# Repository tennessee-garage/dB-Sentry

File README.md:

# dB-Sentry
Sound level monitoring, graphing and alerting for music events

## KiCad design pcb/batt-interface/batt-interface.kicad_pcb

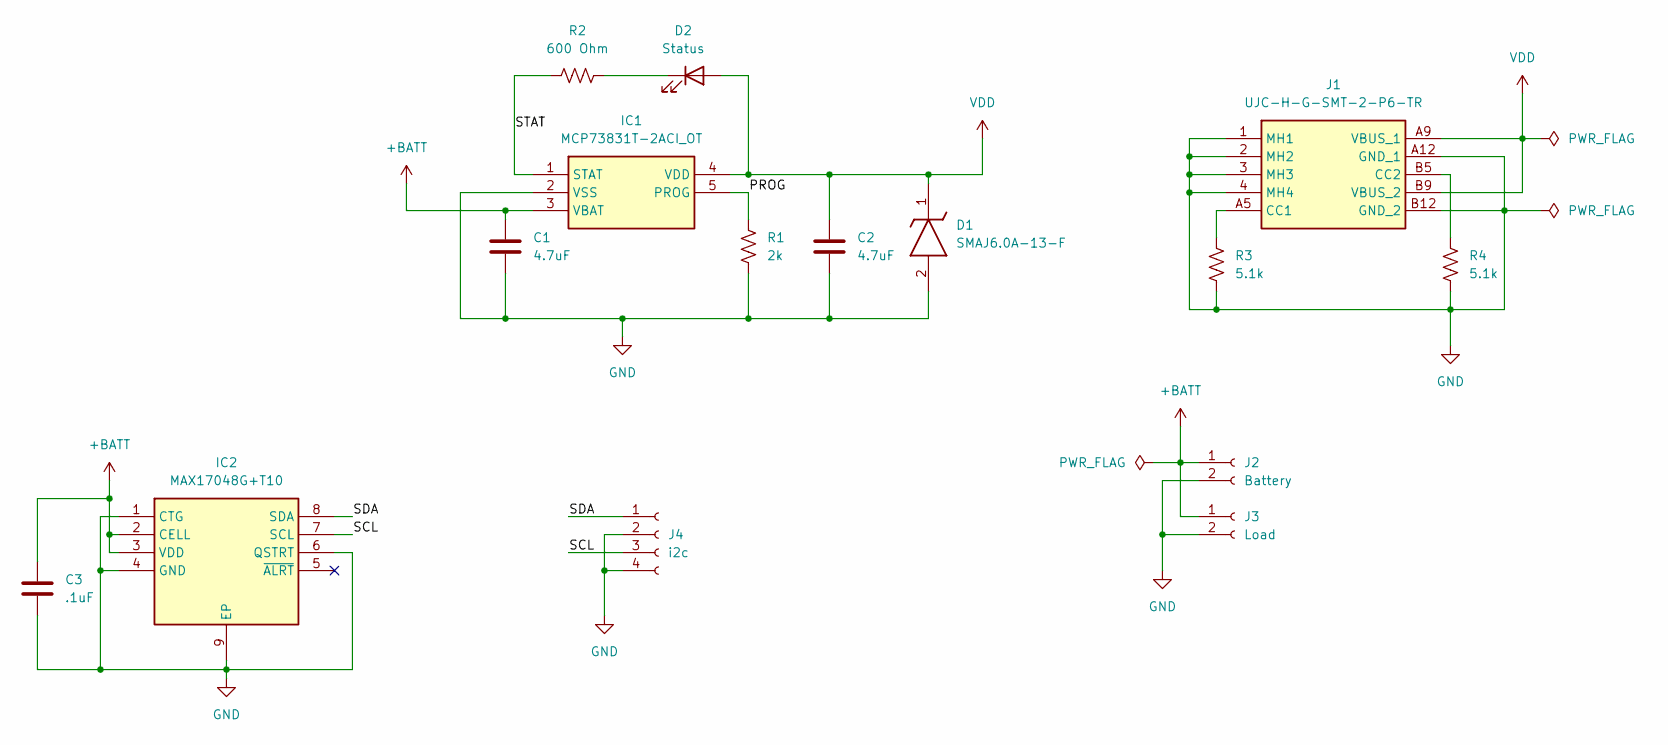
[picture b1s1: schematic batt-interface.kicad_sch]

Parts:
C1, C2: 4.7uF; C_0805_2012Metric_Pad1.18x1.45mm_HandSolder
C3: .1uF; C_0805_2012Metric_Pad1.18x1.45mm_HandSolder
D1: SMAJ6.0A-13-F; DIOM5226X240N; Mouser Part Number 621-SMAJ6.0A-13-F
D2: Status; LED_0805_2012Metric_Pad1.15x1.40mm_HandSolder
IC1: MCP73831T-2ACI_OT; SOT95P270X145-5N; Mouser Part Number 579-MCP73831T-2ACIOT
IC2: MAX17048G+T10; SON50P200X200X80-9N-D; Mouser Part Number 700-MAX17048G+T10
J1: UJC-H-G-SMT-2-P6-TR; UJCHGSMT2P6TR; Mouser Part Number 179-UJCHGSMT2P6TR
J2: Battery; JST_PH_S2B-PH-K_1x02_P2.00mm_Horizontal
J3: Load; JST_PH_S2B-PH-K_1x02_P2.00mm_Horizontal
J4: i2c; PinHeader_1x04_P2.54mm_Vertical
R1: 2k; R_0805_2012Metric_Pad1.20x1.40mm_HandSolder
R2: 600 Ohm; R_0805_2012Metric_Pad1.20x1.40mm_HandSolder
R3, R4: 5.1k; R_0805_2012Metric_Pad1.20x1.40mm_HandSolder

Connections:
+BATT: C1.1, C3.1, IC1.3 (VBAT), IC2.2 (CELL), IC2.3 (VDD), J2.1, J3.1
/PROG: IC1.5 (PROG), R1.1
/SCL: IC2.7 (SCL), J4.3
/SDA: IC2.8 (SDA), J4.1
/STAT: IC1.1 (STAT), R2.1
GND: C1.2, C2.2, C3.2, D1.2 (A), IC1.2 (VSS), IC2.1 (CTG), IC2.4 (GND), IC2.6 (QSTRT), IC2.9 (EP), J1.1 (MH1), J1.2 (MH2), J1.3 (MH3), J1.4 (MH4), J1.A12 (GND_1), J1.B12 (GND_2), J2.2, J3.2, J4.2, J4.4, R1.2, R3.2, R4.2
unnamed: D2.1 (K), R2.2
unnamed: J1.A5 (CC1), R3.1
unnamed: J1.B5 (CC2), R4.1
VDD: C2.1, D1.1 (K), D2.2 (A), IC1.4 (VDD), J1.A9 (VBUS_1), J1.B9 (VBUS_2)

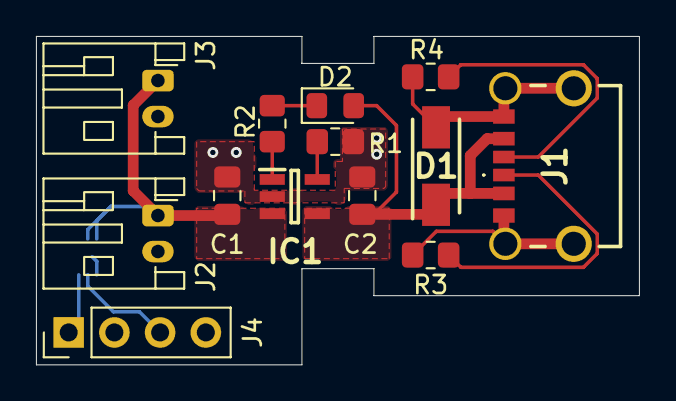
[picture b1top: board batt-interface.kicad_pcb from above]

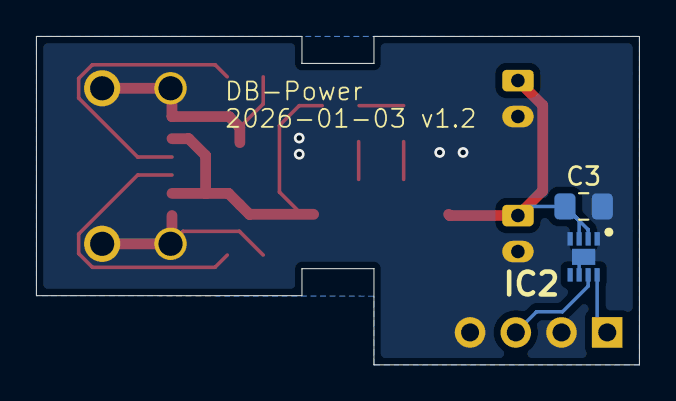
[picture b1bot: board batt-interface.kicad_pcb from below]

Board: 2 copper layers, 33.5 x 18.2 mm, 15 parts (2 on the bottom side), 10 nets.

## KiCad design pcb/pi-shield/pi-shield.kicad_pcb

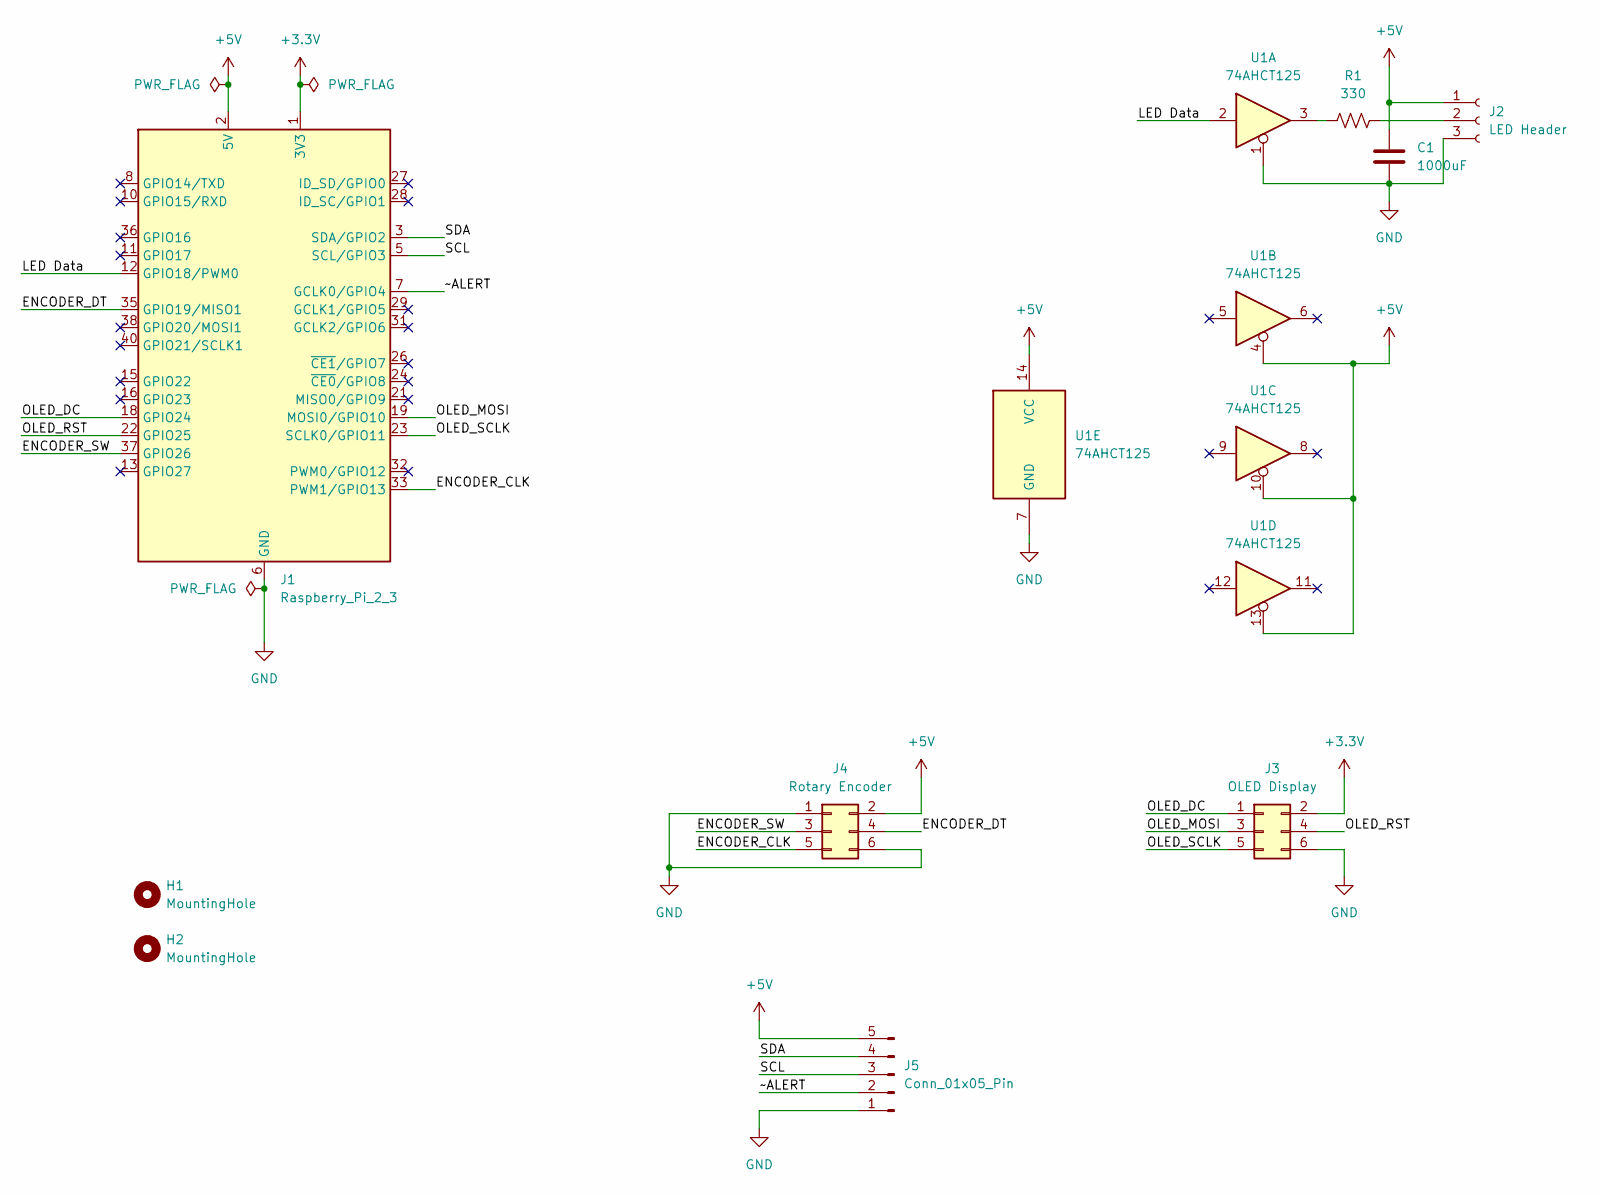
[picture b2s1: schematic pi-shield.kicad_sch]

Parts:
C1: 1000uF; C_Radial_D10.0mm_H16.0mm_P5.00mm
H1, H2: MountingHole; MountingHole_2.7mm_M2.5
J1: Raspberry_Pi_2_3; PinSocket_2x20_P2.54mm_Vertical
J2: LED Header; PinHeader_1x03_P2.54mm_Vertical
J3: OLED Display; PinHeader_2x03_P2.54mm_Vertical
J4: Rotary Encoder; PinHeader_2x03_P2.54mm_Vertical
J5: Conn_01x05_Pin; PinHeader_1x05_P2.54mm_Vertical
R1: 330; R_0805_2012Metric_Pad1.20x1.40mm_HandSolder
U1: 74AHCT125; TSSOP-14_4.4x5mm_P0.65mm

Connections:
+3.3V: J1.1 (3V3), J1.17 (3V3), J3.2
+5V: C1.1, J1.2 (5V), J1.4 (5V), J2.1, J4.2, J5.5, U1.4, U1.10, U1.13, U1.14 (VCC)
/ENCODER_CLK: J1.33 (PWM1/GPIO13), J4.5
/ENCODER_DT: J1.35 (GPIO19/MISO1), J4.4
/ENCODER_SW: J1.37 (GPIO26), J4.3
/LED Data: J1.12 (GPIO18/PWM0), U1.2
/OLED_DC: J1.18 (GPIO24), J3.1
/OLED_MOSI: J1.19 (MOSI0/GPIO10), J3.3
/OLED_RST: J1.22 (GPIO25), J3.4
/OLED_SCLK: J1.23 (SCLK0/GPIO11), J3.5
/SCL: J1.5 (SCL/GPIO3), J5.3
/SDA: J1.3 (SDA/GPIO2), J5.4
/~ALERT: J1.7 (GCLK0/GPIO4), J5.2
GND: C1.2, J1.6 (GND), J1.9 (GND), J1.14 (GND), J1.20 (GND), J1.25 (GND), J1.30 (GND), J1.34 (GND), J1.39 (GND), J2.3, J3.6, J4.1, J4.6, J5.1, U1.1, U1.7 (GND)
unnamed: J2.2, R1.2
unnamed: R1.1, U1.3

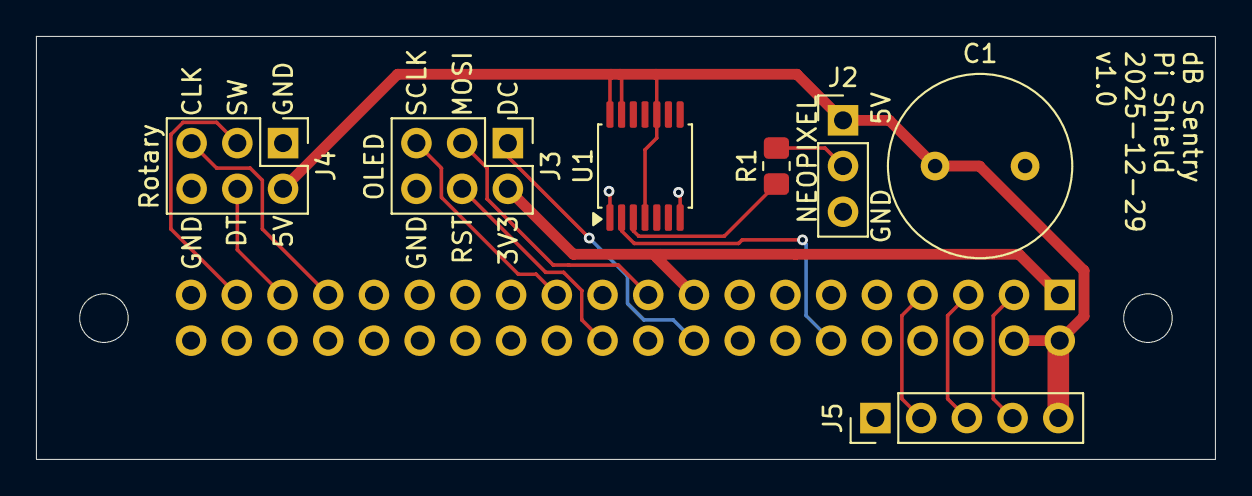
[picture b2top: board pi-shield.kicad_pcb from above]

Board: 2 copper layers, 65.5 x 23.5 mm, 10 parts (1 on the bottom side), 16 nets.

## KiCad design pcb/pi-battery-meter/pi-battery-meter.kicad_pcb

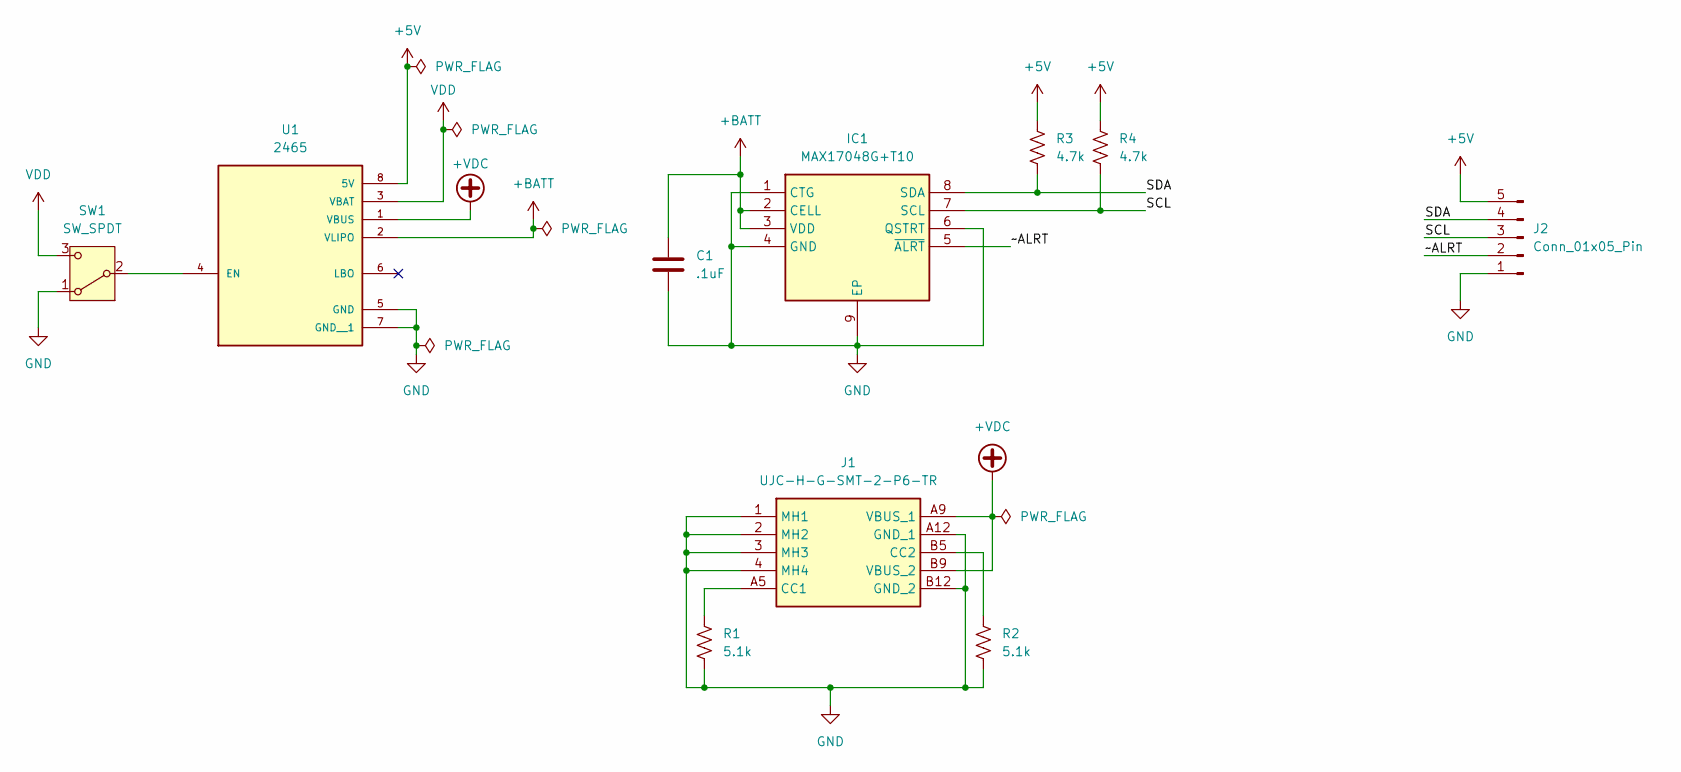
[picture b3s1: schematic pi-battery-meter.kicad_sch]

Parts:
C1: .1uF; C_0805_2012Metric_Pad1.18x1.45mm_HandSolder
IC1: MAX17048G+T10; SON50P200X200X80-9N-D; Mouser Part Number 700-MAX17048G+T10
J1: UJC-H-G-SMT-2-P6-TR; UJCHGSMT2P6TR; Mouser Part Number 179-UJCHGSMT2P6TR
J2: Conn_01x05_Pin; PinHeader_1x05_P2.54mm_Vertical
R1, R2: 5.1k; R_0805_2012Metric_Pad1.20x1.40mm_HandSolder
R3, R4: 4.7k; R_0805_2012Metric_Pad1.20x1.40mm_HandSolder
SW1: SW_SPDT; PinHeader_1x03_P2.54mm_Vertical
U1: 2465; MODULE_2465_NO_PTH; PARTREV B

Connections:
+5V: J2.5, R3.1, R4.1, U1.8 (5V)
+BATT: C1.1, IC1.2 (CELL), IC1.3 (VDD), U1.2 (VLIPO)
+VDC: J1.A9 (VBUS_1), J1.B9 (VBUS_2), U1.1 (VBUS)
/SCL: IC1.7 (SCL), J2.3, R4.2
/SDA: IC1.8 (SDA), J2.4, R3.2
/~ALRT: IC1.5 (~ALRT), J2.2
GND: C1.2, IC1.1 (CTG), IC1.4 (GND), IC1.6 (QSTRT), IC1.9 (EP), J1.1 (MH1), J1.2 (MH2), J1.3 (MH3), J1.4 (MH4), J1.A12 (GND_1), J1.B12 (GND_2), J2.1, R1.2, R2.2, SW1.1 (A), U1.5 (GND), U1.7 (GND__1)
unnamed: J1.A5 (CC1), R1.1
unnamed: J1.B5 (CC2), R2.1
unnamed: SW1.2 (B), U1.4 (EN)
VDD: SW1.3 (C), U1.3 (VBAT)

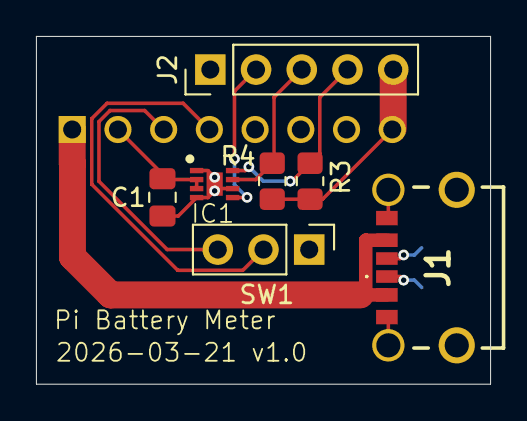
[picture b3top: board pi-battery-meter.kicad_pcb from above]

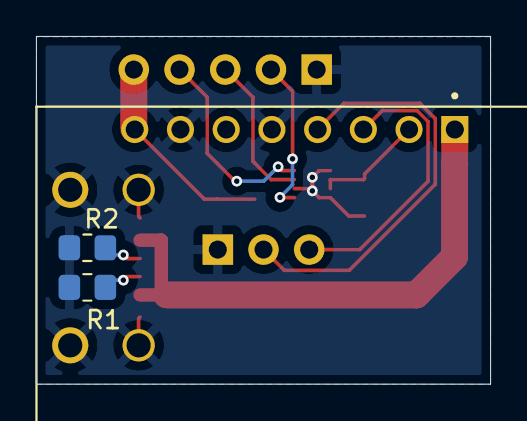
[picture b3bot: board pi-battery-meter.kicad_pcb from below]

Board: 2 copper layers, 25.2 x 19.3 mm, 10 parts (3 on the bottom side), 11 nets.

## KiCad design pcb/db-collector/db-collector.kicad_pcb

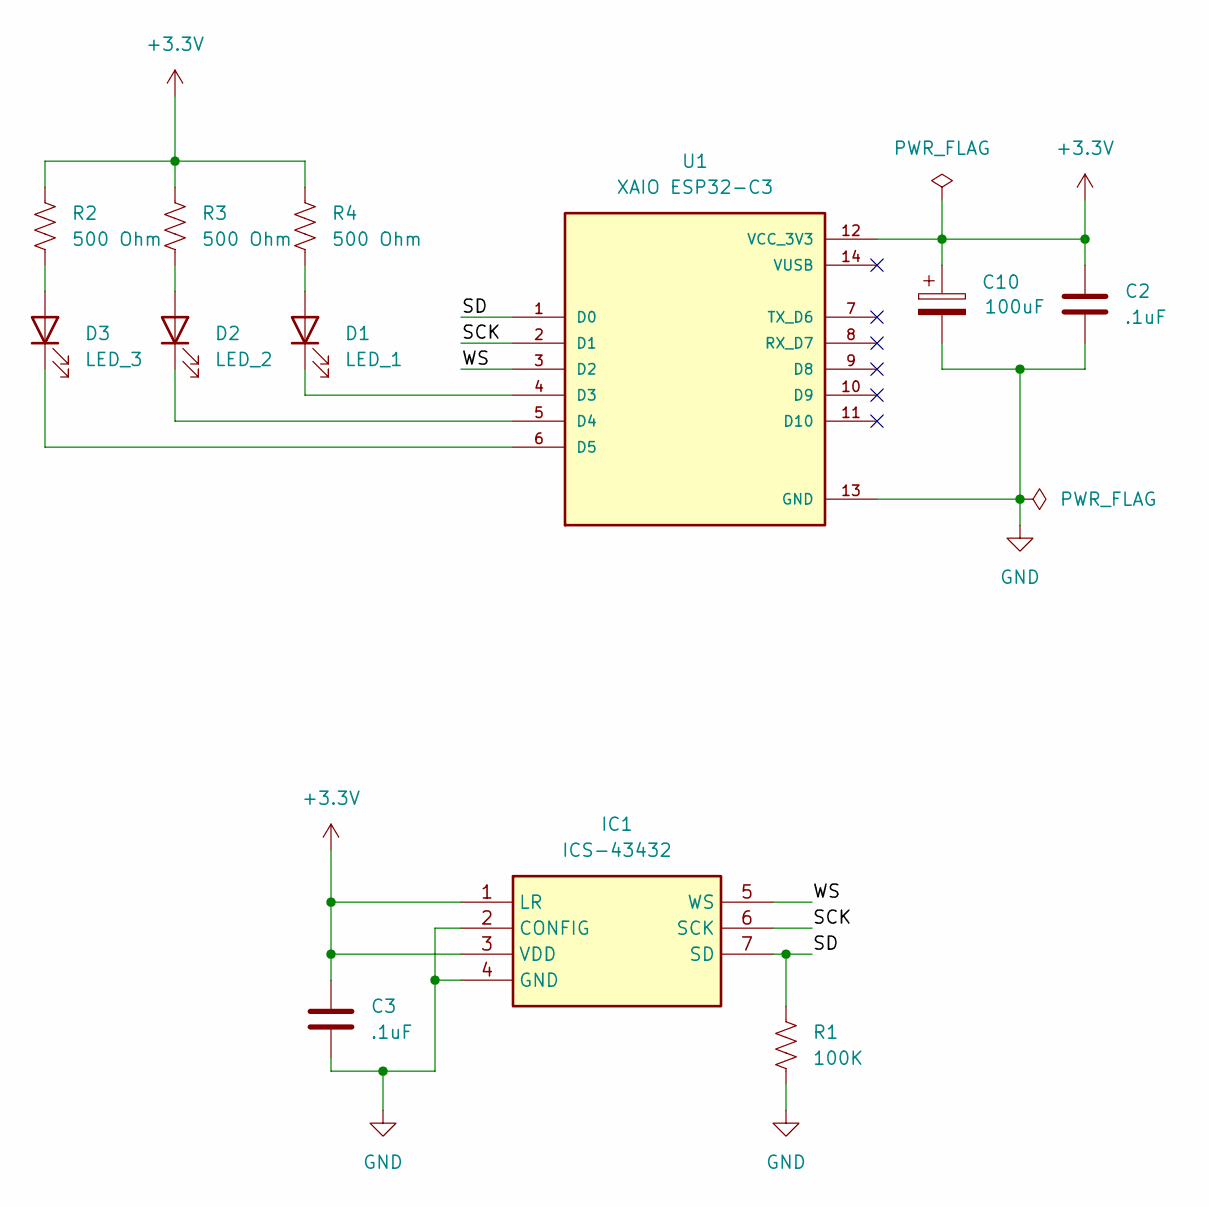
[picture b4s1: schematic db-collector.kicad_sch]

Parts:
C2, C3: .1uF; C_0805_2012Metric_Pad1.18x1.45mm_HandSolder
C10: 100uF; CP_Radial_D5.0mm_P2.00mm
D1: LED_1; PinHeader_1x02_P2.54mm_Vertical
D2: LED_2; PinHeader_1x02_P2.54mm_Vertical
D3: LED_3; PinHeader_1x02_P2.54mm_Vertical
IC1: ICS-43432; ICS43432; Mouser Part Number 410-ICS-43432
R1: 100K; R_0805_2012Metric_Pad1.20x1.40mm_HandSolder
R2, R3, R4: 500 Ohm; R_0805_2012Metric_Pad1.20x1.40mm_HandSolder
U1: XAIO ESP32-C3; MODULE_113991054; PARTREV 23/05/2022

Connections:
+3.3V: C2.1, C3.1, C10.1, IC1.1 (LR), IC1.3 (VDD), R2.1, R3.1, R4.1, U1.12 (VCC_3V3)
/SCK: IC1.6 (SCK), U1.2 (D1)
/SD: IC1.7 (SD), R1.1, U1.1 (D0)
/WS: IC1.5 (WS), U1.3 (D2)
GND: C2.2, C3.2, C10.2, IC1.2 (CONFIG), IC1.4 (GND), R1.2, U1.13 (GND)
unnamed: D1.2 (A), R4.2
unnamed: D1.1 (K), U1.4 (D3)
unnamed: D2.2 (A), R3.2
unnamed: D2.1 (K), U1.5 (D4)
unnamed: D3.2 (A), R2.2
unnamed: D3.1 (K), U1.6 (D5)

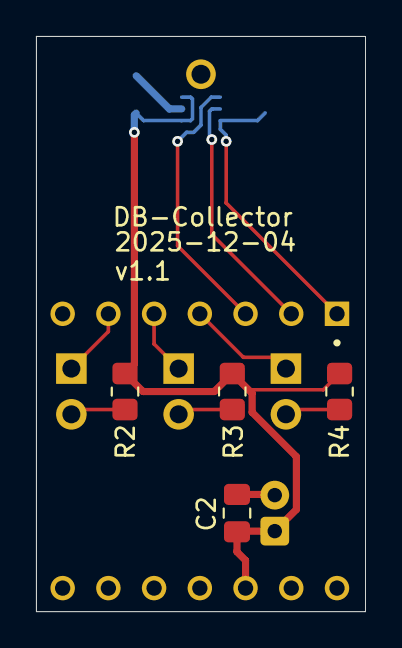
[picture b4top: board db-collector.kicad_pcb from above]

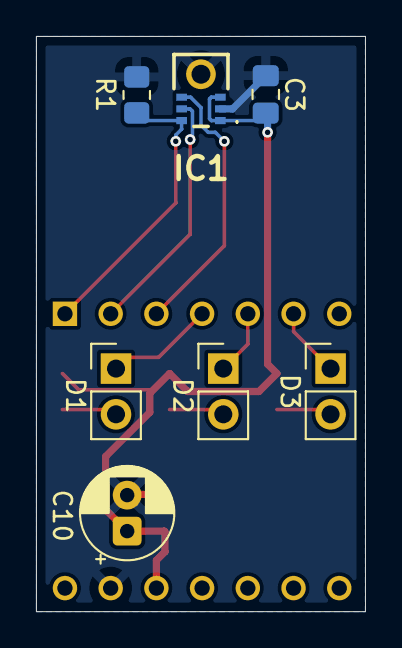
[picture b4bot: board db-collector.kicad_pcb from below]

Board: 2 copper layers, 18.3 x 32.0 mm, 12 parts (7 on the bottom side), 11 nets.

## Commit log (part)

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2025-10-27 First versions of battery board and monitor board
2025-11-07 Ignore mac filesystem stuff
2025-11-11 First version of the db sentry code.
    Mostly test code, but test-mems-lib.cpp does represent working code for the mems microphone, graphing it on vscodes "teleplot".
2025-12-01 First version of python code that monitors the sensor data and alerts
2025-12-01 A few adjustments, more logging around connections
2025-12-01 Make sure we pass through the window seconds value
    Also add some logging
2025-12-01 Correct the topic. Also remove extraneous influxdb connect
2025-12-01 Fix logging calls.
2025-12-01 Actually check for alerting.
2025-12-01 Make sure we're summing the value, not the tuple
2025-12-04 Commiting v1 of this design before making changes for a v2
    Changes in this commit are limited to simple UI view changes, not substantive
2025-12-04 Start a stup script for the limit-service that runs on the pi
    This is to capture some of the things that need to be installed for the limit service to operate
2025-12-04 Updated to use MQTT vs Influx directly
2025-12-04 Remove the Inluxdb handlers
2025-12-04 Adding in embedded shared as a submodule
2025-12-04 Add some logging
2025-12-07 Make sure we inlude all active sensors in the setting list, and give a default value if they haven't been configured yet.
2025-12-07 Write to a table that records alarm state
2025-12-24 Updates to support reading from an encoder
2025-12-24 Adding a service file to start up the dB sentry interfaces
2025-12-24 Pull in the most recent update to wifi in the subproject
2025-12-24 New simplified db-collector. Big change is that the battery attaches directly to the ESP32-c3 XIAO battery terminals and lets it do the voltage regulation. This gets around how finicky the ESP is to 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
2025-12-24 Rename this to something a little shorter
2025-12-24 Update to reflect new name
2025-12-24 Rename
2025-12-24 Forgot more to rename in the readme
2025-12-24 Add the basic oled displayh lib
2025-12-24 Added a some menu item handling, plus a test script for it.
2025-12-24 Try to get SPI running faster
2025-12-24 Make sure to clear before each draw.
2025-12-24 Try to address display ghosting
2025-12-24 Added in support to cache a menu rendering (the font rendering was taking 25ms per line). Also some test scripts that demonstrate a menu, and then one that combines the encoder to control the menu.
2025-12-24 Ignore a bunch of python and mac stuff
2025-12-24 Simplified the oled driver and removed all the animation/easing stuff for scrolling. Also simplified the indexing into the menu cache
2025-12-24 Forgot about the changes to menu.py that support the previous commit. This is primarily the better indexing into the pre-cached frames.
2025-12-24 Cleanup
2026-01-03 Added pull down resistors for CC1 and CC2 to ensure proper charging.
2026-01-04 Add in support for the status LEDs
2026-01-04 First version of the OLED adapter board and the Raspberry Pi shield. These work together to Connect the OLED screen to the Pi, plus a way to connect a rotary encoder.
2026-01-27 Adding real menu options for info and update
2026-01-27 Moving out code for encoder and OLED and leds to a new service
2026-01-27 Fixed some signature errors.
2026-01-27 Get rid of dots
2026-01-27 Fix some menu issues
2026-01-28 Remove old config from when this was copied from the limit-service
2026-01-28 Fix menu live updates and change the brightness settings to be a bar vs number.
2026-01-29 Small refactoring
2026-01-29 Remove vestiges of the interface service, now relocated to its own directory
2026-01-29 Add control for the LED here, and provide an IPC server for the limit-service to connect to us to set warnings/alerts.
2026-01-29 Let me install most things on the mac dev environment
2026-01-29 Create a serice that can be used to run this
2026-01-29 Make the led brightness control work with active feedback from the leds
2026-01-29 Dont' show me errors for this import on a mac
2026-01-30 Updated to remove old LED, OLED and encoder interface stuff which is now in the interface-service.
2026-01-30 Update setup to include installing the service
2026-01-30 Ignore the pycache directories
2026-01-30 Make this script executable
2026-01-30 Make this executable
2026-01-30 Not using pigpiod
2026-01-30 Simplify the interface, get a more readable font.
2026-01-31 Allow the limit-service to update the LEDs with status
2026-01-31 Make sure updates to limits are transfered over to the limit service immediately
2026-01-31 Ignore the user settings file
2026-01-31 Get rid of LED settings
2026-01-31 Add some service management functions
2026-01-31 Adding a menu option to adjust the alert colors
2026-01-31 Move the HSV color utility into its own file.,
2026-02-01 Commit the custom telegraf conf
2026-02-01 Add an IPC to sent sensor information to the interface
2026-02-01 Some small visual fixes.
2026-02-01 Make sure the back button works on dynamic menus
2026-02-01 Don't keep the sensor status display hung at the last known value start showing blank when they're offline.
2026-02-03 Invert scrolling direction
2026-02-03 Fix service name
2026-02-03 Keep track of the last time a sensor sent data, and remove it if its been too long.
2026-02-04 Several changes * Got a more readable font * Displaying 3 lines up now * Adjusted how submenus display * Added methods to the limit-service webserver to allow the interface-service to call it * made 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
2026-02-05 Made all data transfer needed for the OLED menus rely on the limit service webserver API. Anything for updating the LED status bar is from the limit service to the interface service via the IPC servi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
2026-02-05 Updated the Status menu to be more organized. Added a services submenu to list the status of all running services I care about. The AP and IP info, plus ScanAPs could go into a network menu, but Its 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
2026-02-07 Allow adding more readable sensor names, while still making it easy to upload new code to any sensor.
2026-02-07 Add a shutdown menu item
2026-02-07 Move this service earlier in the stack so that the OLED power up. Then show booting text until the limit-service comes online
2026-02-16 First version of setup service
2026-02-16 Create network sub-menu with support for the Setup mode
2026-02-17 Completed setup mode that allows adding WiFi credentials that the Pi and the sensors can use.
2026-02-17 Changes so that the sensors can connect to the db-sentry-hub for setup and for operation.
2026-02-17 Adding in some system services to disable that are default on.
2026-02-18 Add a reset wifi option in case we need to have it rescan.
2026-02-18 Make sure to open page on Setup AP connect.
2026-02-18 Get the captive portal page up faster
2026-02-18 Don't press a menu item when waking up the screen.
2026-02-18 Try to get the captive portal to really popup
2026-02-18 Those last changes didn't work ...
2026-04-11 Add the pi battery meter board
2026-04-30 Adding some images and models for the sentry enclosures
2026-04-30 Fix problem with screen cut off when orientation is to the right.
2026-04-30 Simple script to monitor the live MQTT data as an EQ display.
2026-04-30 README update to support the monitor-level script
2026-04-30 Several KiCad changes (ngl, not sure what changed here)
